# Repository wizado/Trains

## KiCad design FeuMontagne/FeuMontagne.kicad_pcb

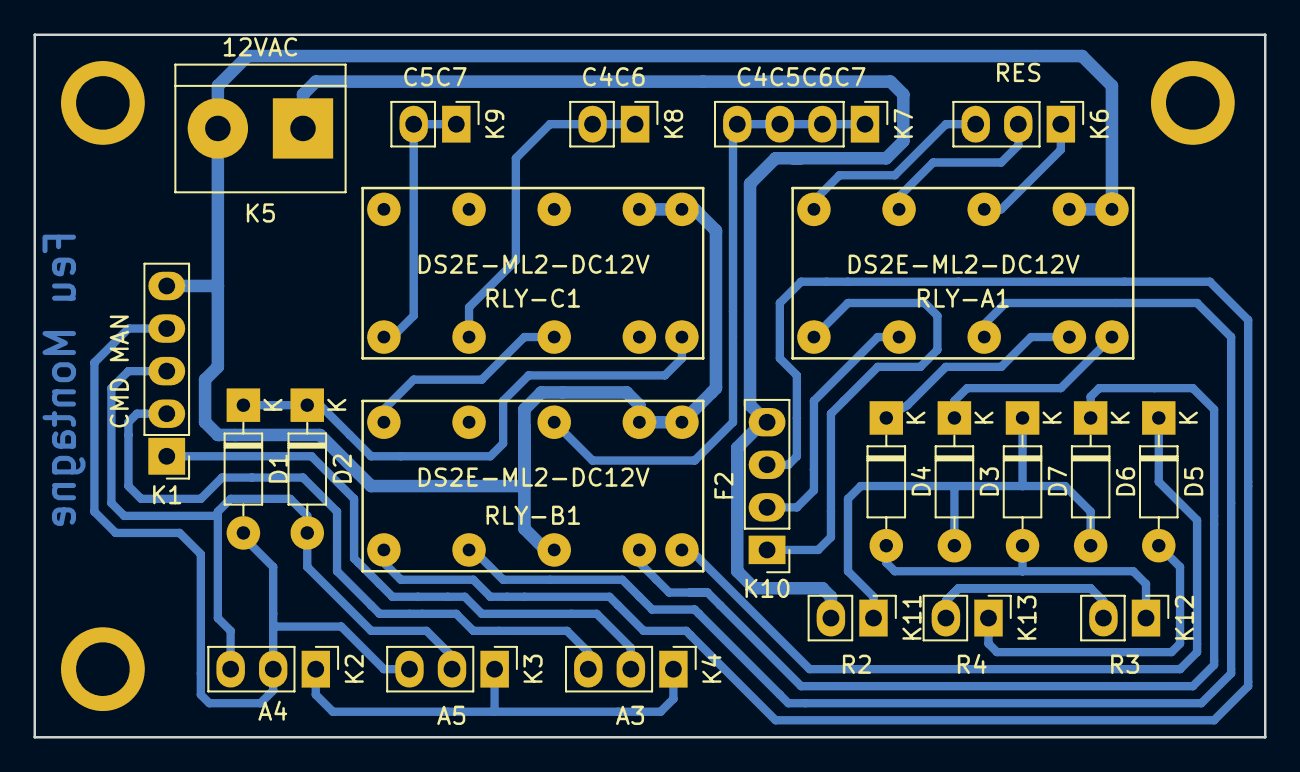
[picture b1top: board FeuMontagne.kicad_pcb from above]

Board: 2 copper layers, 73.4 x 41.9 mm, 23 parts (0 on the bottom side), 27 nets.

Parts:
D1, D2, D3, D4, D5, D6, D7: 1N4148; D_DO-35_SOD27_P7.62mm_Horizontal
K1: CMD MAN; PinHeader_1x05_P2.54mm_Vertical
K2: A4; PinHeader_1x03_P2.54mm_Vertical
K3: A5; PinHeader_1x03_P2.54mm_Vertical
K4: A3; PinHeader_1x03_P2.54mm_Vertical
K5: 12VAC; TerminalBlock_bornier-2_P5.08mm
K6: RES; PinHeader_1x03_P2.54mm_Vertical
K7: C4C5C6C7; PinHeader_1x04_P2.54mm_Vertical
K8: C4C6; PinHeader_1x02_P2.54mm_Vertical
K9: C5C7; PinHeader_1x02_P2.54mm_Vertical
K10: F2; PinHeader_1x04_P2.54mm_Vertical
K11: R2; PinHeader_1x02_P2.54mm_Vertical
K12: R3; PinHeader_1x02_P2.54mm_Vertical
K13: R4; PinHeader_1x02_P2.54mm_Vertical
RLY-A1: DS2E-ML2-DC12V
RLY-B1: DS2E-ML2-DC12V
RLY-C1: DS2E-ML2-DC12V

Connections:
unnamed: D1.1, D2.1, RLY-C1.1
unnamed: D1.2, K1.4, K2.2, K3.3
unnamed: D2.2, K1.3, K2.3, K3.2
unnamed: D3.1, RLY-A1.1
unnamed: D3.2, D6.2, D7.1, K11.1
unnamed: D4.1, RLY-A1.2
unnamed: D4.2, D7.2, K12.1
unnamed: D5.1, RLY-B1.1
unnamed: D5.2, K13.1
unnamed: D6.1, RLY-B1.2
unnamed: K1.1, K4.2
unnamed: K1.2, K4.3
unnamed: K1.5, K5.2, RLY-A1.15, RLY-A1.16, RLY-B1.4, RLY-B1.15, RLY-B1.16, RLY-C1.15, RLY-C1.16
unnamed: K2.1, K3.1, K4.1
unnamed: K6.1, RLY-A1.13
unnamed: K6.2, RLY-A1.11
unnamed: K6.3, RLY-A1.9
unnamed: K7.1, K7.2, K7.3, K7.4, RLY-B1.13
unnamed: K8.1, K8.2, RLY-C1.6
unnamed: K9.1, K9.2, RLY-C1.8
unnamed: K10.1, RLY-A1.8
unnamed: K10.2, RLY-A1.6
unnamed: K10.3, RLY-B1.8
unnamed: K5.1, K10.4, K11.2
unnamed: K12.2, K13.2
unnamed: RLY-A1.4, RLY-B1.6
unnamed: RLY-B1.9, RLY-C1.4

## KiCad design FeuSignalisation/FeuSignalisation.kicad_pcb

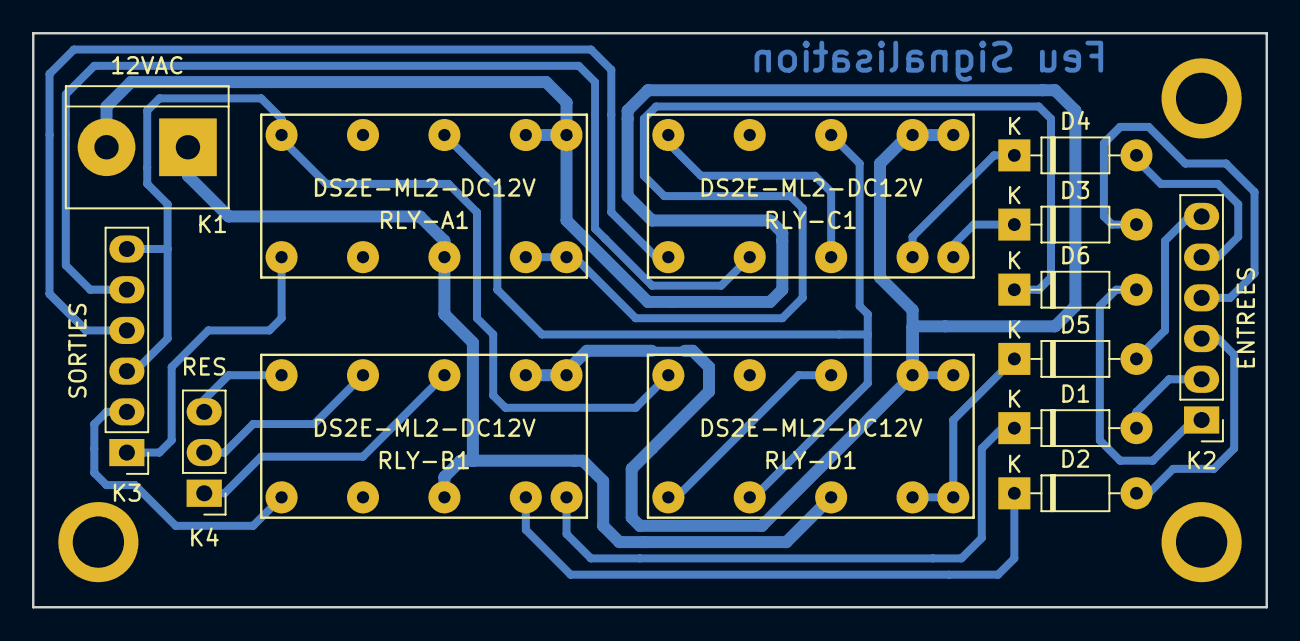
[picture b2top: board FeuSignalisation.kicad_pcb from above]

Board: 2 copper layers, 77.0 x 35.8 mm, 14 parts (0 on the bottom side), 25 nets.

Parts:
D1, D2, D3, D4, D5, D6: 1N4148; D_DO-35_SOD27_P7.62mm_Horizontal
K1: 12VAC; TerminalBlock_bornier-2_P5.08mm
K2: ENTREES; PinHeader_1x06_P2.54mm_Vertical
K3: SORTIES; PinHeader_1x06_P2.54mm_Vertical
K4: RES; PinHeader_1x03_P2.54mm_Vertical
RLY-A1: DS2E-ML2-DC12V
RLY-B1: DS2E-ML2-DC12V
RLY-C1: DS2E-ML2-DC12V
RLY-D1: DS2E-ML2-DC12V

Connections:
unnamed: D1.1, RLY-B1.1
unnamed: D1.2, K2.2
unnamed: D2.1, RLY-B1.2
unnamed: D2.2, K2.3
unnamed: D3.1, RLY-C1.1
unnamed: D3.2, K2.4
unnamed: D4.1, RLY-C1.2
unnamed: D4.2, K2.5
unnamed: D5.1, RLY-D1.1, RLY-D1.2
unnamed: D5.2, K2.6
unnamed: D6.1, RLY-A1.1, RLY-A1.2
unnamed: D6.2, K2.1
unnamed: K1.1, RLY-A1.4, RLY-B1.4, RLY-D1.4
unnamed: K1.2, RLY-A1.15, RLY-A1.16, RLY-B1.15, RLY-B1.16, RLY-C1.15, RLY-C1.16, RLY-D1.15, RLY-D1.16
unnamed: K3.1, RLY-A1.8
unnamed: K3.2, RLY-B1.8
unnamed: K3.3, K3.6, RLY-A1.9, RLY-D1.9
unnamed: K3.4, RLY-C1.8
unnamed: K3.5, RLY-C1.6
unnamed: K4.1, RLY-B1.13
unnamed: K4.2, RLY-B1.11
unnamed: K4.3, RLY-B1.9
unnamed: RLY-A1.13, RLY-C1.13, RLY-D1.6
unnamed: RLY-C1.4, RLY-C1.9
unnamed: RLY-D1.8, RLY-D1.13

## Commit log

2020-03-21 Update schematic
2020-04-21 PCB terminées !
2020-04-22 Corrections
    Une erreur + changement des pastilles pour réalisation à la main plus facile + ajout du nom des cartes coté soudure
